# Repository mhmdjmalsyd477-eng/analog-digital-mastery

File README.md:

# 🚀 Engineering Portfolio: Full Stack Analog, Mixed-Signal & Digital Design

سجل هندسي يوثق رحلتي في تصميم الأنظمة الإلكترونية، من مستوى الترانزستور وصولاً إلى الـ Embedded Systems. هذا المستودع يمثل رؤيتي كـ **Full Stack Hardware Engineer**، حيث أقوم ببناء الدوائر، محاكاتها، أتمتتها، ثم تنفيذها كمنتج متكامل على PCB.

## 📚 المراجع الأكاديمية (Academic References)
لضمان الدقة العلمية في كل خطوة، أعتمد على المراجع التالية كأساس نظري:
- **Analog & Microelectronics:** *Fundamentals of Microelectronics* (3rd Edition) - **Behzad Razavi**.
- **Advanced Analog IC Design:** *Design of Analog CMOS Integrated Circuits* (2nd Edition) - **Behzad Razavi**.
- **Semiconductor Physics:** *Solid State Electronic Devices* (7th Edition) - **Ben G. Streetman & Sanjay Kumar Banerjee**.

## 🏆 المشروع المتكامل (Capstone Project)
### 3-Bit Flash Analog-to-Digital Converter (ADC)
مشروع يربط بين التصميم التناظري (Analog IC)، معالجة الإشارات الرقمية، وتصميم الـ PCB، مع بناء أدوات أتمتة (ADT) خاصة لكل مرحلة. هذا المشروع هو تطبيق عملي على رحلة التصميم الكاملة (Full Stack Flow).

## 📬 تواصل معي (Get in Touch)
يسعدني التواصل لمناقشة المشاريع الهندسية، تبادل الخبرات، أو فرص التعاون:

LinkedIn: https://www.linkedin.com/in/mohammed-gamal-2400768m

Email: mhmdjmalsyd477@gmail.com

تم الإنشاء بواسطة: محمد جمال سيد محمد سليمان 

## 📂 هيكل المستودع (Repository Structure)
```text
/analog-digital-mastery
├── analog-ic/                      
│   └── labs/
│       ├── xschem-ngspice/
│       ├── adt/
│       ├── cadence-virtuoso/
│       └── mentor/
├── digital-design/                 
│   └── labs/
├── mixed-signal-design/            
│   └── 3-bit-flash-adc/
├── embedded-systems/               
│   ├── labs/
│   └── projects/
├── pcb-design/                     
│   ├── kicad/
│   └── easyeda/
└── adt-scripts/
```

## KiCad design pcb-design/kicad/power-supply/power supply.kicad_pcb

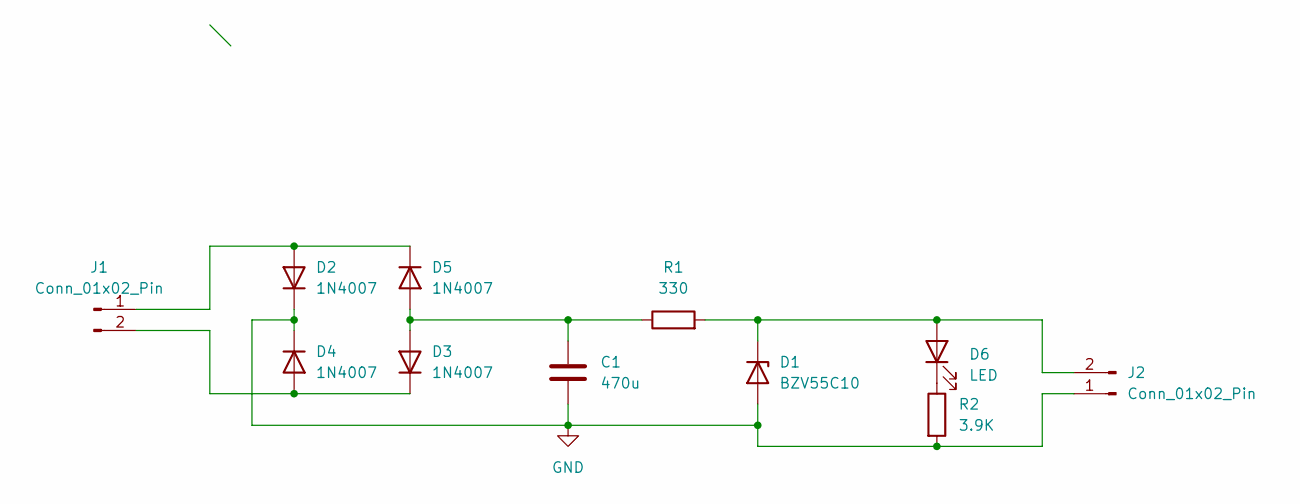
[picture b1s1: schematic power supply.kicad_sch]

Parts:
C1: 470u; CP_Radial_D8.0mm_P3.50mm
D1: BZV55C10; D_MiniMELF
D2, D3, D4, D5: 1N4007; D_DO-41_SOD81_P10.16mm_Horizontal
D6: LED; LED_D3.0mm_Horizontal_O3.81mm_Z10.0mm
J1, J2: Conn_01x02_Pin; PinHeader_1x02_P2.54mm_Vertical
R1: 330; R_Axial_DIN0204_L3.6mm_D1.6mm_P7.62mm_Horizontal
R2: 3.9K; R_Axial_DIN0204_L3.6mm_D1.6mm_P7.62mm_Horizontal

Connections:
GND: C1.1, D1.2 (A), D2.1 (K), D4.1 (K), J2.1, R2.2
unnamed: D1.1 (K), D6.2 (A), J2.2, R1.2
unnamed: D2.2 (A), D5.1 (K), J1.1
unnamed: C1.2, D3.2 (A), D5.2 (A), R1.1
unnamed: D3.1 (K), D4.2 (A), J1.2
unnamed: D6.1 (K), R2.1

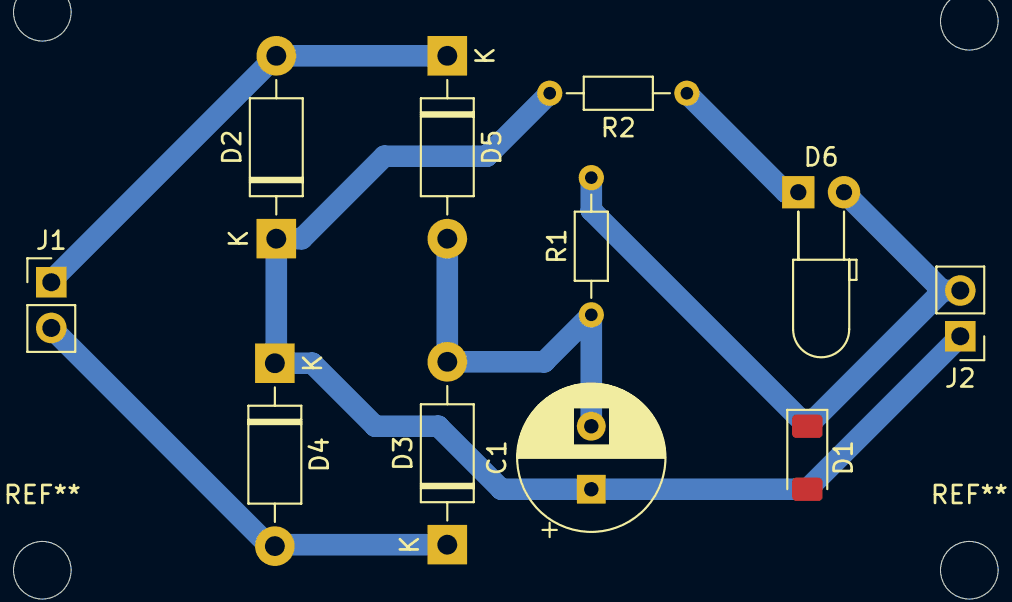
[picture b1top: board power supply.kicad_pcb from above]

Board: 2 copper layers, 11 parts (0 on the bottom side), 6 nets.
